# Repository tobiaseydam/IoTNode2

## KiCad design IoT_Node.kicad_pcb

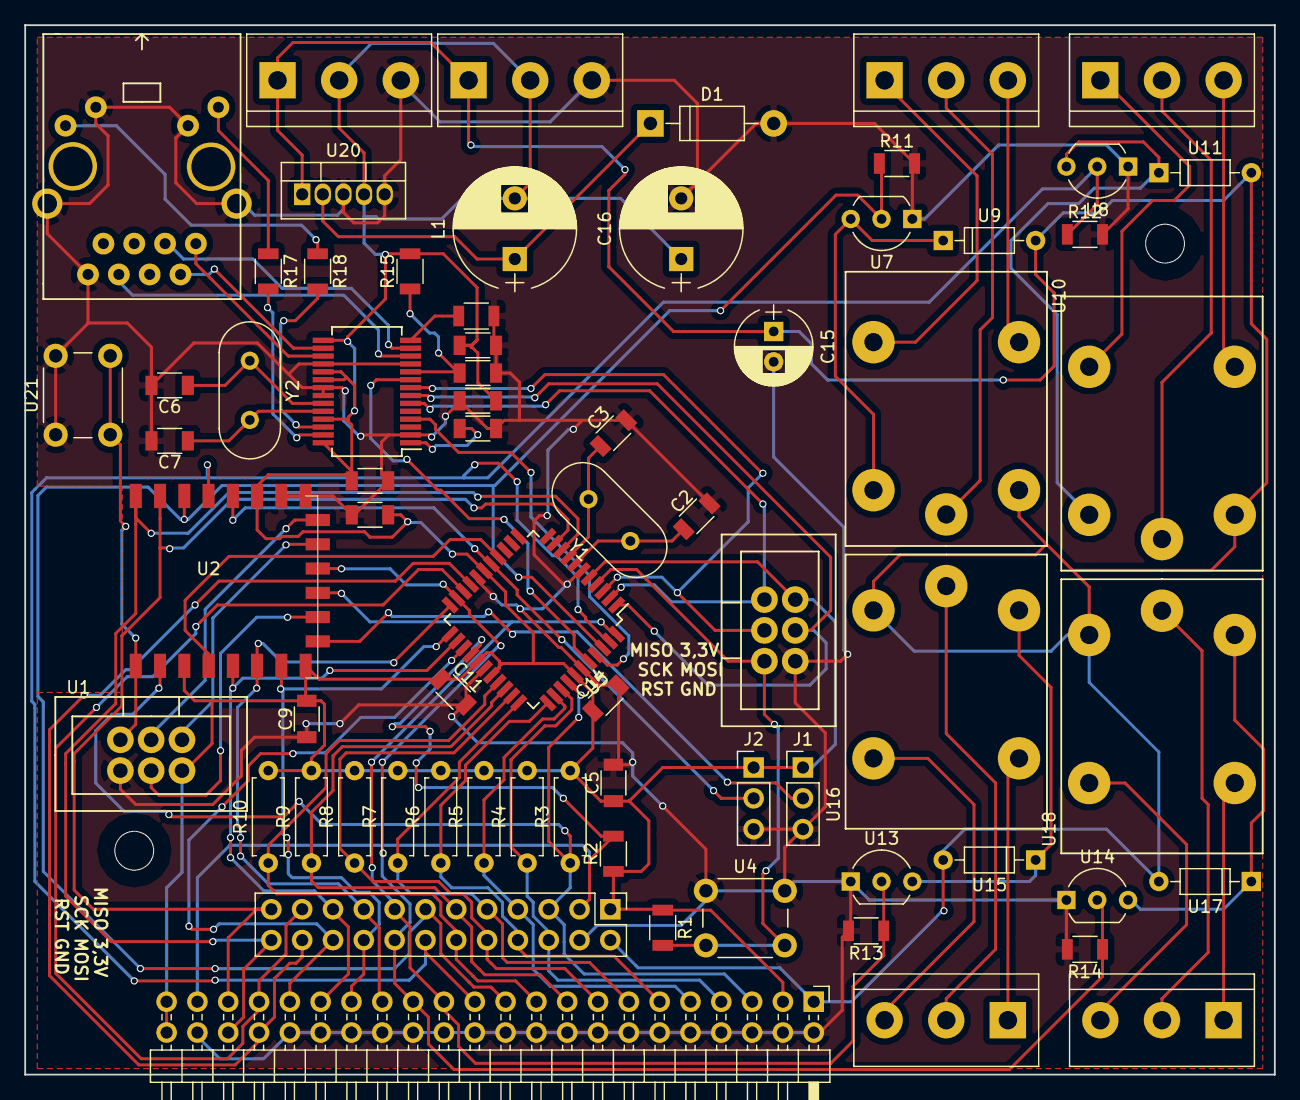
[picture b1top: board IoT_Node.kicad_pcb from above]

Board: 2 copper layers, 103.0 x 86.5 mm, 69 parts (0 on the bottom side), 69 nets.

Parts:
C1, C4, C5, C8, C9, C10, C11, C13, C14: 100n; C_1206
C2, C3: 22p; C_1206
C6, C7: 18p; C_1206
C12: 10µ; C_1206
C15: 100µ; CP_Radial_D6.3mm_P2.50mm
C16: 330µ; CP_Radial_D10.0mm_P5.00mm
D1: 1N5819; D_DO-41_SOD81_P10.16mm_Horizontal
J1, J2: Conn_01x03; Pin_Header_Straight_1x03_Pitch2.54mm
J3, J4, J5, J6, J8, J9: Conn_01x03; TerminalBlock_bornier-3_P5.08mm
J7: RJ45-TRANSFO; RJ45-WIZnet
J10: IOT2Connector_Int; Pin_Header_Straight_2x12_Pitch2.54mm
L1: 330µ; CP_Radial_D10.0mm_P5.00mm
R1, R11, R12, R13, R14: 10k; R_1206
R2: 4k7; R_1206
R3, R4, R5, R6, R7, R8, R9, R10: R_Axial_DIN0207_L6.3mm_D2.5mm_P7.62mm_Horizontal
R15: 33k; R_1206
R16: 2k; R_1206
R17, R18: 180; R_1206
U1, U3: ICSP6
U2: ESP-12E; ESP-12E_SMD
U4, U21: Button; SW_PUSH_6mm
U5: ATMEGA324A-AU; TQFP-44_10x10mm_Pitch0.8mm
U6: IOT2Connector; Pin_Header_Angled_2x22_Pitch2.54mm
U7, U8, U13, U14: MOSFET; TO-92_Inline_Wide
U9, U11, U15, U17: 1N4148; D_DO-35_SOD27_P7.62mm_Horizontal
U10, U12, U16, U18: Relay; Relais_Omron_Electronics_Inc-EMC_Div_G5LE-14
U19: ENC28J60-C/SS; SSOP-28_5.3x10.2mm_Pitch0.65mm
U20: LM2575; TO-220-5_Vertical
Y1: 10MHz; Crystal_HC49-U_Vertical
Y2: 25MHz; Crystal_HC49-U_Vertical

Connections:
+3V3: C1.1, C4.1, C5.1, C9.2, C10.1, C11.1, C13.1, C14.1, C16.1, J1.1, J2.1, J8.2, J9.2, J10.1, L1.2, R1.1, R2.1, R3.2, R4.2, R5.2, R6.2, R7.2, R8.2, R9.2, R10.2, R15.2, U1.2, U2.3, U2.8, U2.11, U3.2, U5.5, U5.17, U5.27, U5.29, U5.38, U6.3, U6.43, U6.44, U19.15, U19.19, U19.20, U19.25, U19.28, U20.4
+12V: C15.1, J8.1, J9.1, J10.2, U6.1, U9.2, U10.5, U11.2, U12.5, U15.2, U16.5, U17.2, U18.5, U20.1
/1wire: J10.3, R2.2, U5.26, U6.41
/ACD2: J10.7, R5.1, U5.35, U6.9
/ADC0: J10.5, R3.1, U2.2, U5.37, U6.5
/ADC1: J10.6, R4.1, U5.36, U6.7
/ADC3: J10.8, R6.1, U5.34, U6.11
/ADC4: J10.9, R7.1, U5.33, U6.13
/ADC5: J10.10, R8.1, U5.32, U6.15
/ADC6: J10.11, R9.1, U5.31, U6.17
/ADC7: J10.12, R10.1, U5.30, U6.19
/ESP_BOOT: J2.2, U2.12, U5.16
/ESP_CS0: J1.2, U2.17
/ESP_SLEEP: U2.4, U5.15
/ETH_CS: U5.40, U19.9
/ETH_INT: U5.41, U19.4
/I2C_SCL: J10.22, U5.19, U6.38
/I2C_SDA: J10.21, U5.20, U6.37
/IO0: J10.13, R11.1, U2.14, U5.42, U6.21, U7.2
/IO1: J10.14, R12.1, U2.13, U5.43, U6.23, U8.2
/IO2: J10.15, R13.1, U2.19, U5.44, U6.25, U13.2
/IO3: J10.16, R14.1, U2.20, U5.21, U6.27, U14.2
/IO4: J10.17, U2.6, U5.22, U6.29
/IO5: J10.18, U2.7, U5.23, U6.31
/IO6: J10.19, U2.5, U5.24, U6.33
/IO7: J10.20, U5.25, U6.35
/MISO1: U3.1, U5.2, U19.6
/MISO2: U1.1, U2.21
/MOSI1: U3.4, U5.1, U19.7
/MOSI2: U1.4, U2.18
/RST1: R1.2, U3.5, U4.2, U5.4
/RST2: U1.5, U2.1, U21.2
/RXD: J10.24, U2.16, U5.9, U6.40
/SCK1: U3.3, U5.3, U19.8
/SCK2: U1.3, U2.22
/TXD: J10.23, U2.15, U5.10, U6.39
/enc28j60/LEDA: R17.2, U19.27
/enc28j60/LEDB: R18.2, U19.26
/enc28j60/TPIN+: J7.4, U19.13
/enc28j60/TPIN-: J7.6, U19.12
/enc28j60/TPOUT+: J7.1, U19.17
/enc28j60/TPOUT-: J7.3, U19.16
GND: C1.2, C2.2, C3.2, C4.2, C5.2, C6.2, C7.2, C8.2, C9.1, C10.2, C11.2, C12.2, C13.2, C14.2, C15.2, C16.2, D1.2, J1.3, J2.3, J7.8, J7.13, J7.GK, J7.YK, J8.3, J9.3, J10.4, R11.2, R12.2, R13.2, R14.2, R16.1, U1.6, U2.9, U2.10, U3.6, U4.1, U5.6, U5.18, U5.28, U5.39, U6.2, U6.4, U6.6, U6.8, U6.10, U6.12, U6.14, U6.16, U6.18, U6.20, U6.22, U6.24, U6.26, U6.28, U6.30, U6.32, U6.34, U6.36, U6.42, U7.1, U8.1, U13.1, U14.1, U19.2, U19.11, U19.18, U19.21, U19.22, U20.3, U20.5, U21.1
unnamed: C2.1, U5.7, Y1.1
unnamed: C3.1, U5.8, Y1.2
unnamed: C6.1, U19.23, Y2.1
unnamed: C7.1, U19.24, Y2.2
unnamed: C8.1, R15.1, U19.10
unnamed: C12.1, U19.1
unnamed: D1.1, L1.1, U20.2
unnamed: J3.1, U10.3
unnamed: J3.2, U10.1
unnamed: J3.3, U10.4
unnamed: J4.1, U12.3
unnamed: J4.2, U12.1
unnamed: J4.3, U12.4
unnamed: J5.1, U16.3
unnamed: J5.2, U16.1
unnamed: J5.3, U16.4
unnamed: J6.1, U18.3
unnamed: J6.2, U18.1
unnamed: J6.3, U18.4
unnamed: J7.GA, R17.1
unnamed: J7.YA, R18.1
unnamed: R16.2, U19.14
unnamed: U7.3, U9.1, U10.2
unnamed: U8.3, U11.1, U12.2
unnamed: U13.3, U15.1, U16.2
unnamed: U14.3, U17.1, U18.2

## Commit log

2018-01-28 board erweitert
2018-03-28 erste Funktionierende Version
